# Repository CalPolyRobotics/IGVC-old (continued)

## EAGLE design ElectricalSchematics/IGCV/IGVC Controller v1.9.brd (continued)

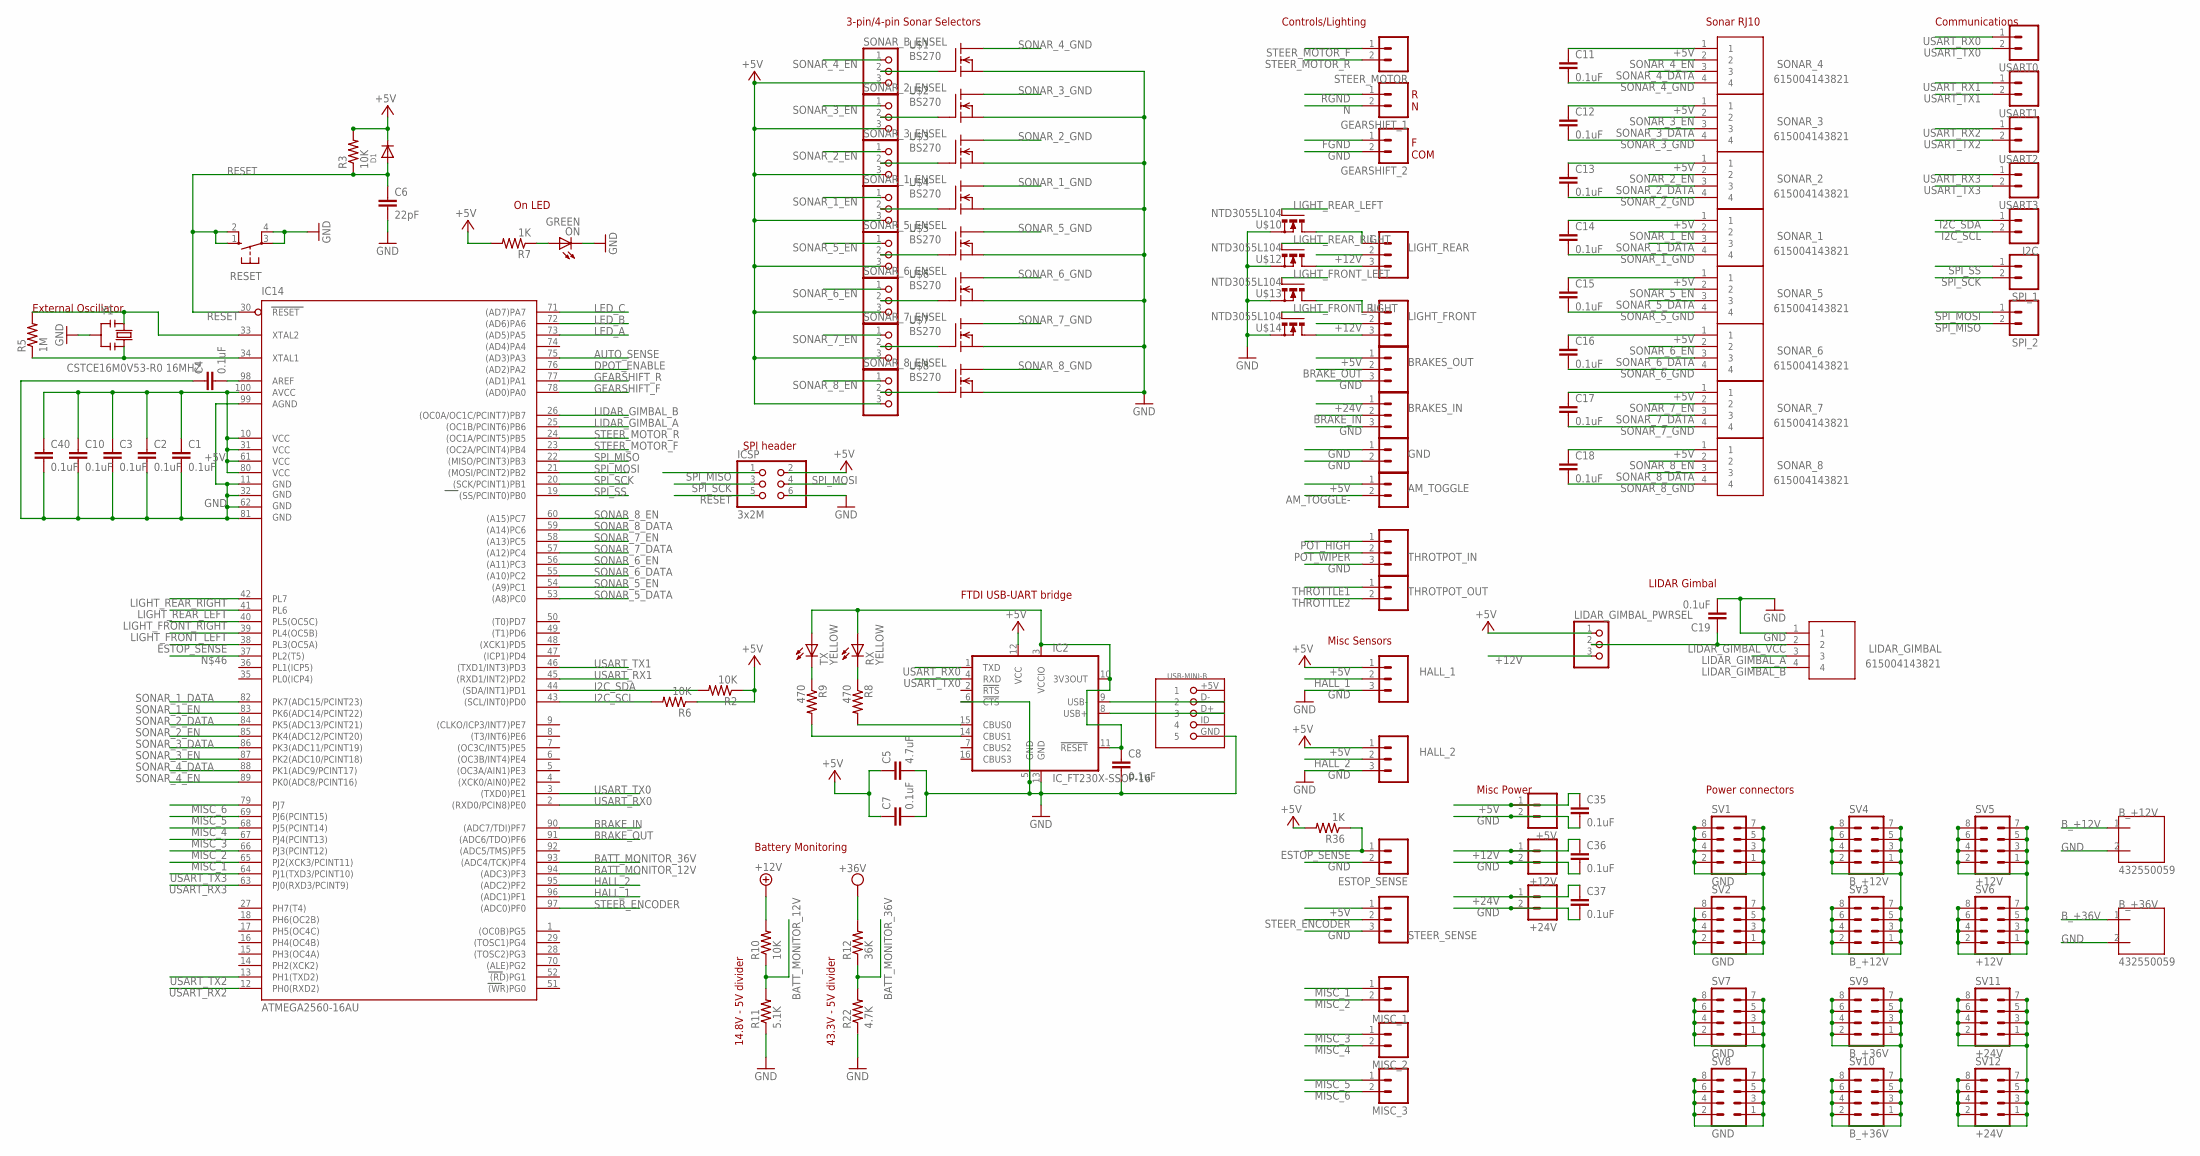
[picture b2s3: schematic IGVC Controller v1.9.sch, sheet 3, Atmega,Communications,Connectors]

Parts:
+5V, +12V, +24V: M02; 02P
AM_TOGGLE: M02; 02P
BRAKES_IN: M03; 03P
BRAKES_OUT: M03; 03P
B_+12V, B_+36V: 432550059
C1, C2, C3, C4, C7, C8, C10, C11, C12, C13, C14, C15, C16, C17, C18, C19, C35, C36, C37, C40: 0.1uF; C0603
C5: 4.7uF; C0603
C6: 22pF; C0603
D1: DIODESOD-323F; SOD-323F
ESTOP_SENSE: M02; 02P
GEARSHIFT_1, GEARSHIFT_2: M02; 02P
GND: M02; 02P
HALL_1, HALL_2: M03; 03P
I2C: M02; 02P
IC2: IC_FT230X-SSOP-16; SSOP-16-FTDI
IC14: ATMEGA2560-16AU; TQFP100
ICSP: 3x2M; 2X03
LIDAR_GIMBAL: 615004143821
LIDAR_GIMBAL_PWRSEL: PINHD-1X3; 1X03
LIGHT_FRONT: M03; 03P
LIGHT_REAR: M03; 03P
MISC_1, MISC_2, MISC_3: M02; 02P
ON: GREEN; CHIP-LED0603
R2, R3, R6, R10: 10K; R0603
R5: 1M; R0603
R7, R36: 1K; R0603
R8, R9: 470; R0603
R11: 5.1K; R0603
R12: 36K; R0603
R22: 4.7K; R0603
RESET: 10-XX; B3F-10XX
RX: YELLOW; CHIP-LED0603
SONAR_1, SONAR_2, SONAR_3, SONAR_4, SONAR_5, SONAR_6, SONAR_7, SONAR_8: 615004143821
SONAR_1_ENSEL, SONAR_2_ENSEL, SONAR_3_ENSEL, SONAR_5_ENSEL, SONAR_6_ENSEL, SONAR_7_ENSEL, SONAR_8_ENSEL: PINHD-1X3; 1X03
SONAR_B_ENSEL: PINHD-1X3; 1X03
SPI_1, SPI_2: M02; 02P
STEER_MOTOR: M02; 02P
STEER_SENSE: M03; 03P
SV1, SV2, SV7, SV8: GND; MA04-2
SV3, SV4: B_+12V; MA04-2
SV5, SV6: +12V; MA04-2
SV9, SV10: B_+36V; MA04-2
SV11, SV12: +24V; MA04-2
THROTPOT_IN: M03; 03P
THROTPOT_OUT: M02; 02P
TX: YELLOW; CHIP-LED0603
U$1, U$2, U$3, U$4, U$5, U$6, U$7, U$8: BS270; TO92-DGS
U$9: USB-MINI-B
U$10, U$12, U$13, U$14: NTD3055L104; TO220-GDS
USART0, USART1, USART2, USART3: M02; 02P
Y1: CSTCE16M0V53-R0 16MHZ; RESONATOR

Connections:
+3.3V: C8.1, IC2.3 (VCCIO), IC2.10 (3V3OUT), IC2.11 (!RESET), RX.A, TX.A
+5V: +5V.1, AM_TOGGLE.1, BRAKES_OUT.1, C1.1, C2.1, C3.1, C5.1, C7.1, C10.1, C11.1, C12.1, C13.1, C14.1, C15.1, C16.1, C17.1, C18.1, C35.1, C40.1, D1.C, HALL_1.1, HALL_2.1, IC2.12 (VCC), IC14.10 (VCC), IC14.31 (VCC1), IC14.61 (VCC2), IC14.80 (VCC3), IC14.100 (AVCC), ICSP.2, LIDAR_GIMBAL_PWRSEL.1, R2.1, R3.2, R6.1, R7.2, R36.2, SONAR_1.1, SONAR_1_ENSEL.3, SONAR_2.1, SONAR_2_ENSEL.3, SONAR_3.1, SONAR_3_ENSEL.3, SONAR_4.1, SONAR_5.1, SONAR_5_ENSEL.3, SONAR_6.1, SONAR_6_ENSEL.3, SONAR_7.1, SONAR_7_ENSEL.3, SONAR_8.1, SONAR_8_ENSEL.3, SONAR_B_ENSEL.3, STEER_SENSE.1; also elsewhere on the board
+12V: +12V.1, C36.1, LIDAR_GIMBAL_PWRSEL.3, LIGHT_FRONT.2, LIGHT_REAR.2, SV5.1, SV5.2, SV5.3, SV5.4, SV5.5, SV5.6, SV5.7, SV5.8, SV6.1, SV6.2, SV6.3, SV6.4, SV6.5, SV6.6, SV6.7, SV6.8; also elsewhere on the board
+24V: +24V.1, BRAKES_IN.1, C37.1, SV11.1, SV11.2, SV11.3, SV11.4, SV11.5, SV11.6, SV11.7, SV11.8, SV12.1, SV12.2, SV12.3, SV12.4, SV12.5, SV12.6, SV12.7, SV12.8; also elsewhere on the board
AM_TOGGLE-: AM_TOGGLE.2; also elsewhere on the board
AUTO_SENSE: IC14.75 ((AD3)PA3); also elsewhere on the board
BATT_MONITOR_12V: IC14.94 ((ADC3)PF3), R10.1, R11.2; also elsewhere on the board
BATT_MONITOR_36V: IC14.93 ((ADC4/TCK)PF4), R12.1, R22.2; also elsewhere on the board
BRAKE_IN: BRAKES_IN.2, IC14.90 ((ADC7/TDI)PF7); also elsewhere on the board
BRAKE_OUT: BRAKES_OUT.2, IC14.91 ((ADC6/TDO)PF6); also elsewhere on the board
B_+12V: B_+12V.1, R10.2, SV3.1, SV3.2, SV3.3, SV3.4, SV3.5, SV3.6, SV3.7, SV3.8, SV4.1, SV4.2, SV4.3, SV4.4, SV4.5, SV4.6, SV4.7, SV4.8; also elsewhere on the board
B_+36V: B_+36V.1, R12.2, SV9.1, SV9.2, SV9.3, SV9.4, SV9.5, SV9.6, SV9.7, SV9.8, SV10.1, SV10.2, SV10.3, SV10.4, SV10.5, SV10.6, SV10.7, SV10.8; also elsewhere on the board
DPOT_ENABLE: IC14.76 ((AD2)PA2); also elsewhere on the board
ESTOP_SENSE: ESTOP_SENSE.1, IC14.38 (PL3(OC5A)), R36.1; also elsewhere on the board
FGND: GEARSHIFT_2.1; also elsewhere on the board
GEARSHIFT_F: IC14.78 ((AD0)PA0); also elsewhere on the board
GEARSHIFT_R: IC14.77 ((AD1)PA1); also elsewhere on the board
GND: +5V.2, +12V.2, +24V.2, BRAKES_IN.3, BRAKES_OUT.3, B_+12V.2, B_+36V.2, C1.2, C2.2, C3.2, C4.1, C5.2, C6.2, C7.2, C8.2, C10.2, C19.2, C35.2, C36.2, C37.2, C40.2, ESTOP_SENSE.2, GEARSHIFT_2.2, GND.1, GND.2, HALL_1.3, HALL_2.3, IC2.5 (GND), IC2.6 (!CTS), IC2.13 (GND), IC14.11 (GND), IC14.32 (GND1), IC14.62 (GND2), IC14.81 (GND3), IC14.99 (AGND), ICSP.6, LIDAR_GIMBAL.1, ON.C, R11.1, R22.1, RESET.3, RESET.4 (P1), STEER_SENSE.3, SV1.1, SV1.2, SV1.3, SV1.4, SV1.5, SV1.6, SV1.7, SV1.8, SV2.1, SV2.2, SV2.3, SV2.4, SV2.5, SV2.6, SV2.7, SV2.8, SV7.1, SV7.2, SV7.3, SV7.4, SV7.5, SV7.6, SV7.7, SV7.8, SV8.1, SV8.2, SV8.3, SV8.4, SV8.5, SV8.6, SV8.7, SV8.8, THROTPOT_IN.3, U$1.S, U$2.S, U$3.S, U$4.S, U$5.S, U$6.S, U$7.S, U$8.S, U$9.GND (5), U$10.S, U$12.S, U$13.S, U$14.S, Y1.2; also elsewhere on the board
HALL_1: HALL_1.2, IC14.96 ((ADC1)PF1); also elsewhere on the board
HALL_2: HALL_2.2, IC14.95 ((ADC2)PF2); also elsewhere on the board
I2C_SCL: I2C.2, IC14.43 ((SCL/INT0)PD0), R6.2; also elsewhere on the board
I2C_SDA: I2C.1, IC14.44 ((SDA/INT1)PD1), R2.2; also elsewhere on the board
LED_A: IC14.73 ((AD5)PA5); also elsewhere on the board
LED_B: IC14.72 ((AD6)PA6); also elsewhere on the board
LED_C: IC14.71 ((AD7)PA7); also elsewhere on the board
LIDAR_GIMBAL_A: IC14.25 ((OC1B/PCINT6)PB6), LIDAR_GIMBAL.3; also elsewhere on the board
LIDAR_GIMBAL_B: IC14.26 ((OC0A/OC1C/PCINT7)PB7), LIDAR_GIMBAL.4; also elsewhere on the board
LIDAR_GIMBAL_VCC: C19.1, LIDAR_GIMBAL.2, LIDAR_GIMBAL_PWRSEL.2; also elsewhere on the board
LIGHT_FRONT_LEFT: IC14.39 (PL4(OC5B)), U$13.G; also elsewhere on the board
LIGHT_FRONT_RIGHT: IC14.40 (PL5(OC5C)), U$14.G; also elsewhere on the board
LIGHT_REAR_LEFT: IC14.41 (PL6), U$10.G; also elsewhere on the board
LIGHT_REAR_RIGHT: IC14.42 (PL7), U$12.G; also elsewhere on the board
MISC_1: IC14.65 (PJ2(XCK3/PCINT11)), MISC_1.1
MISC_2: IC14.66 (PJ3(PCINT12)), MISC_1.2
MISC_3: IC14.67 (PJ4(PCINT13)), MISC_2.1
MISC_4: IC14.68 (PJ5(PCINT14)), MISC_2.2
MISC_5: IC14.69 (PJ6(PCINT15)), MISC_3.1
MISC_6: IC14.79 (PJ7), MISC_3.2
N: GEARSHIFT_1.2; also elsewhere on the board
unnamed: SONAR_B_ENSEL.2, U$1.G
unnamed: SONAR_2_ENSEL.2, U$2.G
unnamed: SONAR_3_ENSEL.2, U$3.G
unnamed: SONAR_1_ENSEL.2, U$4.G
unnamed: SONAR_5_ENSEL.2, U$5.G
unnamed: SONAR_6_ENSEL.2, U$6.G
unnamed: SONAR_7_ENSEL.2, U$7.G
unnamed: SONAR_8_ENSEL.2, U$8.G
unnamed: C4.2, IC14.98 (AREF)
unnamed: ON.A, R7.1
unnamed: IC14.34 (XTAL1), R5.1, Y1.3
unnamed: IC14.33 (XTAL2), R5.2, Y1.1
unnamed: LIGHT_FRONT.3, U$14.D
unnamed: IC2.15 (CBUS0), R8.2
unnamed: IC2.14 (CBUS1), R9.2
unnamed: R9.1, TX.C
unnamed: R8.1, RX.C
unnamed: IC2.9 (USB-), U$9.D- (2)
unnamed: IC2.8 (USB+), U$9.D+ (3)
unnamed: LIGHT_REAR.1, U$10.D
unnamed: LIGHT_REAR.3, U$12.D
unnamed: LIGHT_FRONT.1, U$13.D
POT_HIGH: THROTPOT_IN.1; also elsewhere on the board
POT_WIPER: THROTPOT_IN.2; also elsewhere on the board
RESET: C6.1, D1.A, IC14.30 (RESET), ICSP.5, R3.1, RESET.1 (S), RESET.2 (S1)
RGND: GEARSHIFT_1.1; also elsewhere on the board
SONAR_1_DATA: IC14.82 (PK7(ADC15/PCINT23)), SONAR_1.3; also elsewhere on the board
SONAR_1_EN: IC14.83 (PK6(ADC14/PCINT22)), SONAR_1.2, SONAR_1_ENSEL.1; also elsewhere on the board
SONAR_1_GND: C14.2, SONAR_1.4, U$4.D; also elsewhere on the board
SONAR_2_DATA: IC14.84 (PK5(ADC13/PCINT21)), SONAR_2.3; also elsewhere on the board
SONAR_2_EN: IC14.85 (PK4(ADC12/PCINT20)), SONAR_2.2, SONAR_3_ENSEL.1; also elsewhere on the board
SONAR_2_GND: C13.2, SONAR_2.4, U$3.D; also elsewhere on the board
SONAR_3_DATA: IC14.86 (PK3(ADC11/PCINT19)), SONAR_3.3; also elsewhere on the board
SONAR_3_EN: IC14.87 (PK2(ADC10/PCINT18)), SONAR_2_ENSEL.1, SONAR_3.2; also elsewhere on the board
SONAR_3_GND: C12.2, SONAR_3.4, U$2.D; also elsewhere on the board
SONAR_4_DATA: IC14.88 (PK1(ADC9/PCINT17)), SONAR_4.3; also elsewhere on the board
SONAR_4_EN: IC14.89 (PK0(ADC8/PCINT16)), SONAR_4.2, SONAR_B_ENSEL.1; also elsewhere on the board
SONAR_4_GND: C11.2, SONAR_4.4, U$1.D; also elsewhere on the board
SONAR_5_DATA: IC14.53 ((A8)PC0), SONAR_5.3; also elsewhere on the board
SONAR_5_EN: IC14.54 ((A9)PC1), SONAR_5.2, SONAR_5_ENSEL.1; also elsewhere on the board
SONAR_5_GND: C15.2, SONAR_5.4, U$5.D; also elsewhere on the board
SONAR_6_DATA: IC14.55 ((A10)PC2), SONAR_6.3; also elsewhere on the board
SONAR_6_EN: IC14.56 ((A11)PC3), SONAR_6.2, SONAR_6_ENSEL.1; also elsewhere on the board
SONAR_6_GND: C16.2, SONAR_6.4, U$6.D; also elsewhere on the board
SONAR_7_DATA: IC14.57 ((A12)PC4), SONAR_7.3; also elsewhere on the board
SONAR_7_EN: IC14.58 ((A13)PC5), SONAR_7.2, SONAR_7_ENSEL.1; also elsewhere on the board
SONAR_7_GND: C17.2, SONAR_7.4, U$7.D; also elsewhere on the board
SONAR_8_DATA: IC14.59 ((A14)PC6), SONAR_8.3; also elsewhere on the board
SONAR_8_EN: IC14.60 ((A15)PC7), SONAR_8.2, SONAR_8_ENSEL.1; also elsewhere on the board
SONAR_8_GND: C18.2, SONAR_8.4, U$8.D; also elsewhere on the board
SPI_MISO: IC14.22 ((MISO/PCINT3)PB3), ICSP.1, SPI_2.2; also elsewhere on the board
SPI_MOSI: IC14.21 ((MOSI/PCINT2)PB2), ICSP.4, SPI_2.1; also elsewhere on the board
SPI_SCK: IC14.20 ((SCK/PCINT1)PB1), ICSP.3, SPI_1.2; also elsewhere on the board
SPI_SS: IC14.19 ((SS/PCINT0)PB0), SPI_1.1; also elsewhere on the board
STEER_ENCODER: IC14.97 ((ADC0)PF0), STEER_SENSE.2; also elsewhere on the board
STEER_MOTOR_F: IC14.23 ((OC2A/PCINT4)PB4), STEER_MOTOR.1; also elsewhere on the board
STEER_MOTOR_R: IC14.24 ((OC1A/PCINT5)PB5), STEER_MOTOR.2; also elsewhere on the board
THROTTLE1: THROTPOT_OUT.1; also elsewhere on the board
THROTTLE2: THROTPOT_OUT.2; also elsewhere on the board
USART_RX0: IC2.1 (TXD), IC14.2 ((RXD0/PCIN8)PE0), USART0.1; also elsewhere on the board
USART_RX1: IC14.45 ((RXD1/INT2)PD2), USART1.1; also elsewhere on the board
USART_RX2: IC14.12 (PH0(RXD2)), USART2.1; also elsewhere on the board
USART_RX3: IC14.63 (PJ0(RXD3/PCINT9)), USART3.1; also elsewhere on the board
USART_TX0: IC2.4 (RXD), IC14.3 ((TXD0)PE1), USART0.2; also elsewhere on the board
USART_TX1: IC14.46 ((TXD1/INT3)PD3), USART1.2; also elsewhere on the board
USART_TX2: IC14.13 (PH1(TXD2)), USART2.2; also elsewhere on the board
USART_TX3: IC14.64 (PJ1(TXD3/PCINT10)), USART3.2; also elsewhere on the board

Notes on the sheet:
Communications
Sonar RJ10
Power connectors
Controls/Lighting
Misc Sensors
LIDAR Gimbal
3-pin/4-pin Sonar Selectors
SPI header
FTDI USB-UART bridge
On LED
External Oscillator
14.8V - 5V divider
43.3V - 5V divider
Battery Monitoring
Misc Power
R N F COM

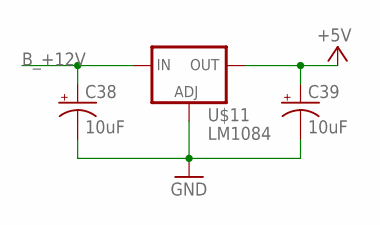
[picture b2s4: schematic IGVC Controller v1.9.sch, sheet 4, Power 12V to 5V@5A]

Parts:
C38, C39: 10uF; B45181B
U$11: LM1084; TO220V

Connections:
+5V: C39.+, U$11.2 (OUT); also elsewhere on the board
B_+12V: C38.+, U$11.3 (IN); also elsewhere on the board
GND: C38.-, C39.-, U$11.1 (ADJ); also elsewhere on the board

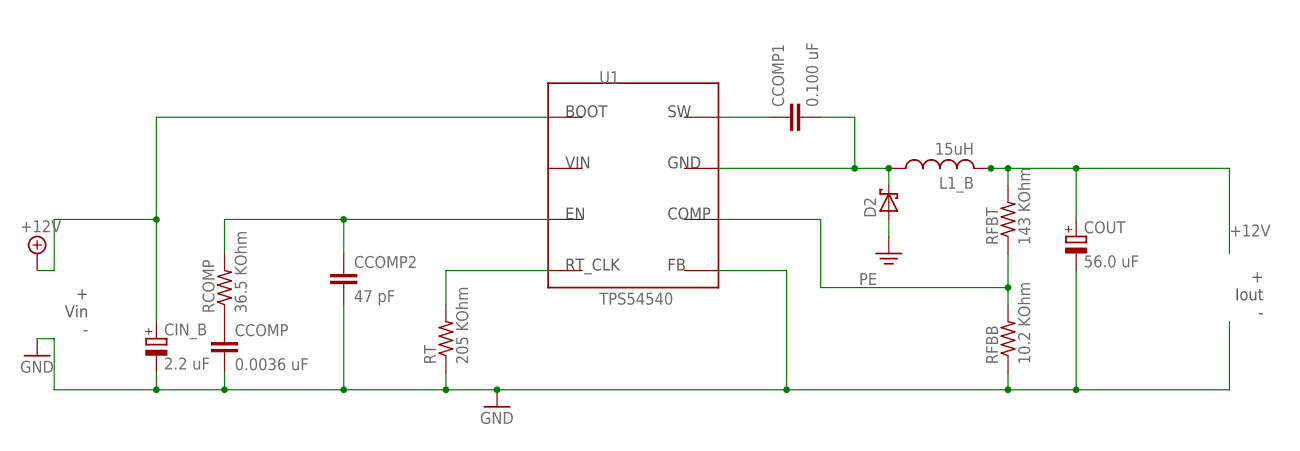
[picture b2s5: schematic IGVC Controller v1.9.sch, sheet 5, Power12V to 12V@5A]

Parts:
CCOMP: 0.0036 uF; C0603
CCOMP1: 0.100 uF; C0603
CCOMP2: 47 pF; C0603
CIN_B: 2.2 uF; E2-5
COUT: 56.0 uF; E2,5-6
D2: SCHOTTKY-DIODE; SOD-128
L1_B: 15uH; TOROID
RCOMP: 36.5 KOhm; R0603
RFBB: 10.2 KOhm; R0603
RFBT: 143 KOhm; R0603
RT: 205 KOhm; R0603
U1: TPS54540; R-PDSO-G8

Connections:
+12V: COUT.+, L1_B.P$2 (2), RFBT.2; also elsewhere on the board
B_+12V: CIN_B.+, U1.VIN; also elsewhere on the board
GND: CCOMP.2, CCOMP2.2, CIN_B.-, COUT.-, D2.A, RFBB.1, RT.1, U1.GND; also elsewhere on the board
unnamed: CCOMP.1, RCOMP.1
unnamed: CCOMP2.1, RCOMP.2, U1.COMP
unnamed: RT.2, U1.RT_CLK
unnamed: CCOMP1.2, D2.C, L1_B.P$1 (1), U1.SW
unnamed: RFBB.2, RFBT.1, U1.FB
unnamed: CCOMP1.1, U1.BOOT

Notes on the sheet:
+ Vin -
+ Iout -

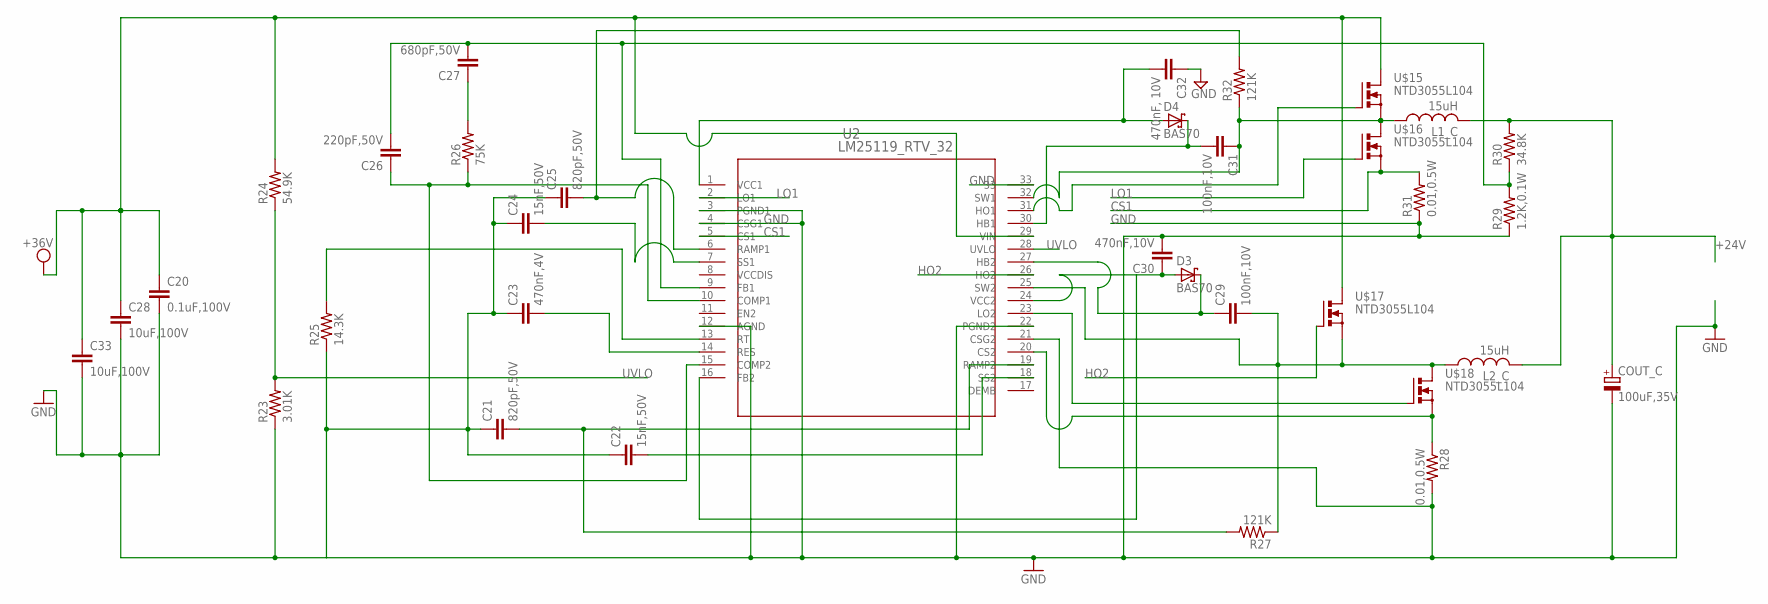
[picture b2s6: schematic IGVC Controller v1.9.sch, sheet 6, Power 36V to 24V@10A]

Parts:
C20: 0.1uF,100V; C0603
C21, C25: 820pF,50V; C0603
C22, C24: 15nF,50V; C0603
C23: 470nF,4V; C0603
C26: 220pF,50V; C0603
C27: 680pF,50V; C0603
C28, C33: 10uF,100V; 5750
C29, C31: 100nF,10V; C0603
C30: 470nF,10V; C0603
C32: 470nF, 10V; C0603
COUT_C: 100uF,35V; E2,5-5
D3, D4: BAS70; SOT23
L1_C, L2_C: 15uH; TOROID
R23: 3.01K; R0603
R24: 54.9K; R0603
R25: 14.3K; R0603
R26: 75K; R0603
R27, R32: 121K; R0603
R28, R31: 0.01,0.5W; R0603
R29: 1.2K,0.1W; R0603
R30: 34.8K; R0603
U2: LM25119_RTV_32; SQA32A
U$15, U$16, U$17, U$18: NTD3055L104; TO220-GDS

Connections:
+24V: COUT_C.+, L1_C.P$2 (2), L2_C.P$2 (2), R30.2; also elsewhere on the board
B_+36V: C20.1, C28.P$1 (1), C33.P$1 (1), R24.2, U2.29 (VIN), U$15.D, U$17.D; also elsewhere on the board
CS1: R31.2, U2.5 (CS1), U$16.S
GND: C20.2, C21.1, C22.1, C23.1, C24.1, C25.1, C28.P$2 (2), C30.2, C32.1, C33.P$2 (2), COUT_C.-, R23.1, R25.1, R28.2, R29.1, R31.1, U2.3 (PGND1), U2.4 (CSG1), U2.12 (AGND), U2.21 (CSG2), U2.22 (PGND2), U2.33; also elsewhere on the board
HO2: U2.26 (HO2), U$17.G
LO1: U2.2 (LO1), U$16.G
unnamed: R25.2, U2.13 (RT)
unnamed: C21.2, R27.2, U2.19 (RAMP2)
unnamed: C26.1, R26.1, U2.10 (COMP1), U2.15 (COMP2)
unnamed: C23.2, U2.14 (RES)
unnamed: C24.2, U2.7 (SS1)
unnamed: C25.2, R32.2, U2.6 (RAMP1)
unnamed: C26.2, C27.2, R29.2, R30.1, U2.9 (FB1)
unnamed: C27.1, R26.2
unnamed: R28.1, U2.20 (CS2), U$18.S
unnamed: C29.2, L2_C.P$1 (1), R27.1, U2.25 (SW2), U$17.S, U$18.D
unnamed: U2.23 (LO2), U$18.G
unnamed: C29.1, D3.3 (C), U2.27 (HB2)
unnamed: C22.2, U2.18 (SS2)
unnamed: C30.1, D3.1 (A), U2.16 (FB2), U2.24 (VCC2)
unnamed: C31.1, L1_C.P$1 (1), R32.1, U2.32 (SW1), U$15.S, U$16.D
unnamed: U2.31 (HO1), U$15.G
unnamed: C31.2, D4.3 (C), U2.30 (HB1)
unnamed: C32.2, D4.1 (A), U2.1 (VCC1)
UVLO: R23.2, R24.1, U2.28 (UVLO)
VCCDIS: U2.8 (VCCDIS)

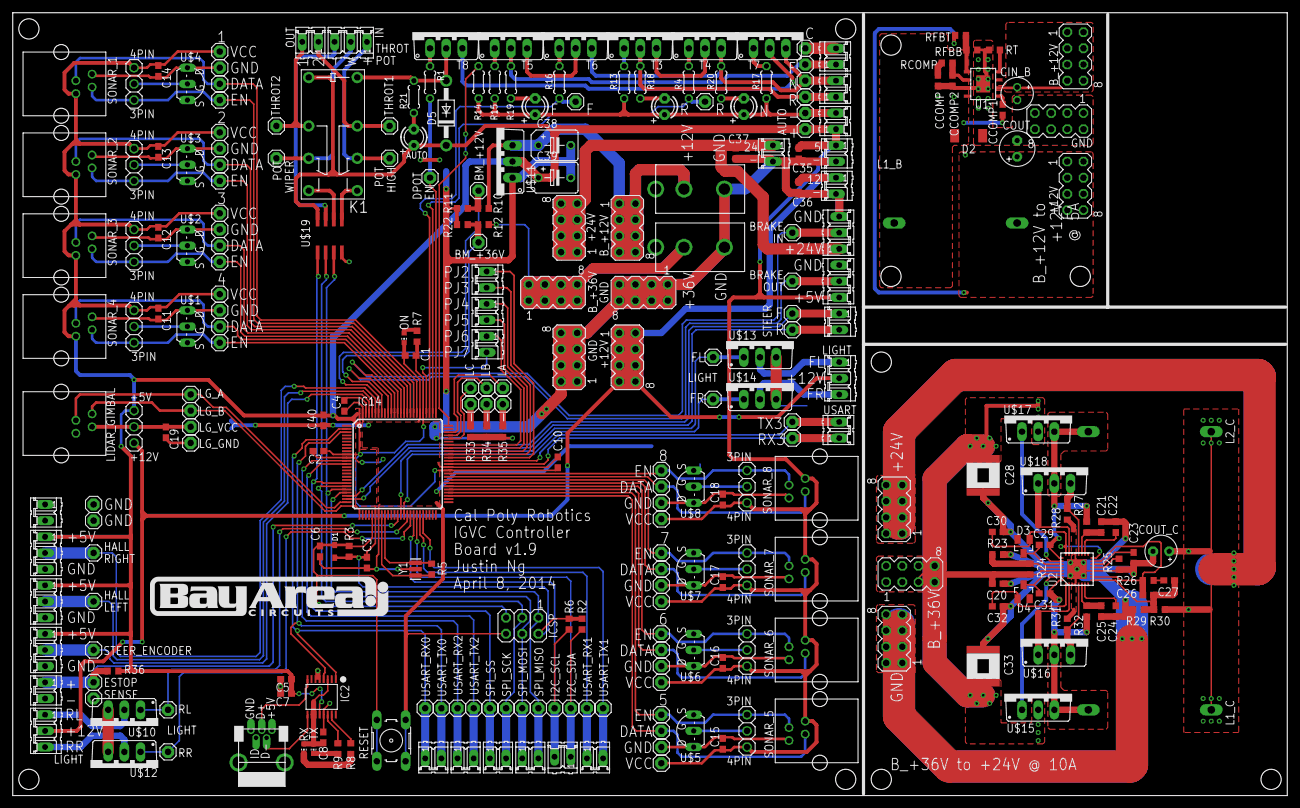
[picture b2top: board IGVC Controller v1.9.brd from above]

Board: 2 copper layers, 200.2 x 122.9 mm, 278 parts (0 on the bottom side), 153 nets.

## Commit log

2014-04-03 Updated eagle schematics and board
    routed PCB and image
2014-04-05 removed build files
2014-04-06 Cleaned build files and directories
2014-04-18 Added more generated files to gitignore
2014-04-20 updated eagle
2014-04-20 Fixed USART stuff. Almost working
2014-04-20 Changed the tick rate
2014-04-23 Revert "Changed the tick rate"
    This reverts commit 440d519edc6385b64bcd1862488cfe094ab1f091.
2014-04-23 Revert "Merge branch 'master' of https://github.com/CalPolyRobotics/IGVC"
    This reverts commit ef79e14682cd38ef4eaeb542e69ae4425c7a2b6d, reversing
    changes made to 440d519edc6385b64bcd1862488cfe094ab1f091.
2014-05-10 Fixed usart code. Works for commands that do not send a payload
2014-05-11 Comm payloads work
2014-05-15 Milestone 1 with real board
2014-05-15 More finalized milestone 1 code
2014-05-17 ADC now works
2014-05-18 Added steering control
2014-06-22 Steering now works with Justin's motor driver
2014-06-22 Everything now compiles with -Werror.
2014-06-22 Added pragma directives to remove warnings
2014-10-04 updated the electrical set up
2014-10-04 good shit
2014-10-04 update library file
    update library file
2014-10-04 added sparkfun eagle librarys
2014-10-04 Updated Schematic
    Moved pins in tms570ls0432 schematic library
2014-10-04 More Updates
2014-10-04 Oscillator
2014-10-04 added mcu populated primary parts and started on ethernet
2014-10-04 update library
2014-10-04 wiznet oscillator
2014-10-04 added ethernet and clocks
2014-10-04 updated ethernet
2014-10-04 updated the library
2014-10-04 added lib
2014-10-04 actually added lib
2014-10-07 break up the parts
2014-10-07 break up the parts more
2014-10-07 122-1734-ND added
2014-10-11 added lm25061
2014-10-11 updated fpga
2014-10-11 FPGA
2014-10-11 updated connector
2014-10-11 Connected Ethernet Connector
2014-10-11 power changes and lib update
2014-10-11 power sch update
2014-10-12 Added supervisor part
2014-10-12 JTAG
2014-10-12 Updated Supervisor
2014-10-12 center JTAG
2014-10-12 added an usb to spi chip
2014-10-12 Created schematics for USB to mcu com and added isolation
2014-10-12 connectors
2014-10-12 connector devices
2014-10-12 Data Isolation FPGA
2014-10-12 Inserted the Batttery monitoring circuit
2014-10-12 added Programmer to fpga
2014-10-12 updated power ethernet and tempatature
2014-10-12 Connectors Schematic
2014-10-12 20 pin JTAG
2014-10-12 MCU JTAG
2014-10-12 updated steeing
2014-10-12 coimbineeded everything
2014-10-13 updated the schematics for the ridgley
2014-10-13 updated mcu
2014-10-13 updated everything
2014-10-14 Fixed Grounds
2014-10-14 Saved Changes
2014-10-14 updated power circuit
2014-10-14 cleaned up power
2014-10-14 cleaned up the ftdi code
2014-10-14 Fixed Temperature Sensors
2014-10-19 Updated Power
2014-10-19 commiting justins changes to the steering controller
2014-10-19 updated the spi to usb convert file
2014-10-19 updated temp
2014-10-19 Added pot to shit
2014-10-19 Change shit's pot and updated power
2014-10-19 CLEANED UP THE MCU
2014-10-19 FPGA style and wiring io
2014-10-19 Start cleaning FNR
2014-10-19 FNR except digipot
2014-10-19 updated circuits
2014-10-19 FNR with digipot
2014-10-19 updated power and ethernet
2014-10-20 updated board2a
2014-10-20 Battery Monitor Finished?
2014-10-20 updated board 2 a
2014-10-20 4dpt switch
2014-10-20 updated more of the schematics
2014-10-21 Added Isolator Library
2014-10-22 updated board
2014-10-22 added relay fets
2014-10-23 updated shit
2014-10-23 Added Analog Connectors
2014-10-23 FPGA and isolation
2014-10-25 Named Sheets in v2a
2014-10-25 Connected a wire.. Q.Q
2014-10-25 Ethernet Changes
2014-10-25 More changes
2014-10-26 Changed Ethernet
2014-10-26 Cleaned things up Shoop da Whoooop
2014-10-26 Lots of validation
2014-10-26 More Validation
2014-10-26 updated fnr
2014-10-26 updated schematics
2014-10-26 Started BOM
2014-10-26 Removed Ultralibrarian Decals
2014-10-27 updated schematatics
2014-10-27 updarted board
2014-10-27 design rules
2014-10-28 did some more routing
2014-10-28 updated changes
2014-10-28 work on lin
2014-10-28 did more changes on placement
2014-10-28 updated stuff
2014-10-28 routed power stuff
2014-10-28 fixed FNR ground
2014-10-29 routed supervisor cleaned up placement
2014-10-29 did some lagit routing
2014-10-29 Made smaller resistor array
2014-10-29 Lots of routing and some lib updates
2014-10-29 cleaned up FPGA
2014-10-30 did more work on fpga
2014-10-30 Fix a bunch
2014-10-30 moves all the new parts into place
2014-10-30 routed lin ethernet and usb
2014-10-30 Routed FNR and rerouted some ldos
2014-10-30 fixed decals
2014-10-31 board
2014-10-31 fpga to mcu
2014-10-31 adopting a baby with barney
2014-10-31 Fixed FPGA isolation routing
    TODO: Check the FPGA pin by pin in the datasheet.
2014-11-01 layed out battery
2014-11-01 routed more traces
2014-11-02 routed most of the preliminary bus lines
2014-11-02 Cap Placement and routing
2014-11-02 design rules check
2014-11-02 updated the board
2014-11-02 updated the board cleaned up the traces
2014-11-02 updatd theboard for real
2014-11-02 connector and routing
2014-11-02 updaqted mcu
2014-11-03 fixed up fnr
2014-11-03 cleaned up more routing
2014-11-03 fixed more over laps
2014-11-03 updated battery monitor
2014-11-03 updated the board even more I love computer I hate my lef
2014-11-03 updated common node filter
2014-11-04 cleaned up more of the traces
2014-11-04 almost finished
2014-11-04 almost finished saved now
2014-11-04 fixed usb to spi pads for dfm
2014-11-04 fixed ethernet holes
2014-11-04 fixed usb to spi pads again
2014-11-08 pushing final board
2014-11-16 Implemented rateTracker VHDL
2015-01-17 changed pfets and made version 3 of board
2015-01-17 updated ldo library and some routing
2015-01-18 Motor Driver and MCU changes
